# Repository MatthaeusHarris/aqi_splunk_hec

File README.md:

# Air Quality Data Logger for Splunk

This is the arduino-based firmware for an ESP8266-based device which will monitor air quality by means of a PMS7003 Air Quality Sensor and upload the resulting data to a Splunk HTTP Event Collector.  

## Configuration

On first flash, the device will create its own wifi access point "WifiManager" and wait to be configured.  Simply connect to the access point and open the [Configuration Page](http://192.168.4.1) to configure the device.  All fields are required.  These settings are stored in flash memory and will persist across power cycles.

Settings are as follows:
* Splunk Server: FQDN of the server on which Splunk is running
* Splunk Port:  TCP port on which the HEC is listening
* Token: HEC token
* Index: the Splunk index that will receive this data
* Sourcetype: the sourcetype that shall accompany this data

If a new configuration is required, reboot the device (either with the reboot button on the ESP8266 or via a power cycle), then hold the flash button down for three seconds.  Do not hold the flash button down while rebooting, as this puts the ESP8266 into another mode. 

## Debugging

The device will also log debug information to a serial port on the ESP8266's USB port at 115200,8,N,1.  Once the device is booted, this consists of a single line of data containing the current AQI, PM2.5, and PM10 readings once per second.

## Screen

The TFT_eSPI library is required to compile the firmware, but the device will work without one connected.  The code assumes a 128x128 screen, but should be easy enough to modify if desired.

## Dependencies

This firmware depends on the following libraries:
* TFT_eSPI
* ArduinoJson
* WifiManager

## Wiring

Power the PMSx003 with 5V.  Connect only the TX and RX pins to D3 and D4, respectively.

If you wish to connect an LCD screen, set up your User_Setup.h file according to the screen you are using.  This was tested with a ST7735 green tab 3 screen.

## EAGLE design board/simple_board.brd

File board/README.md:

# Board Files

Eagle 9.2.2, nothing fancy, just routing and layout for a NodeMCU and pin headers for a ST7735 screen and the PMSx003 air quality monitor.

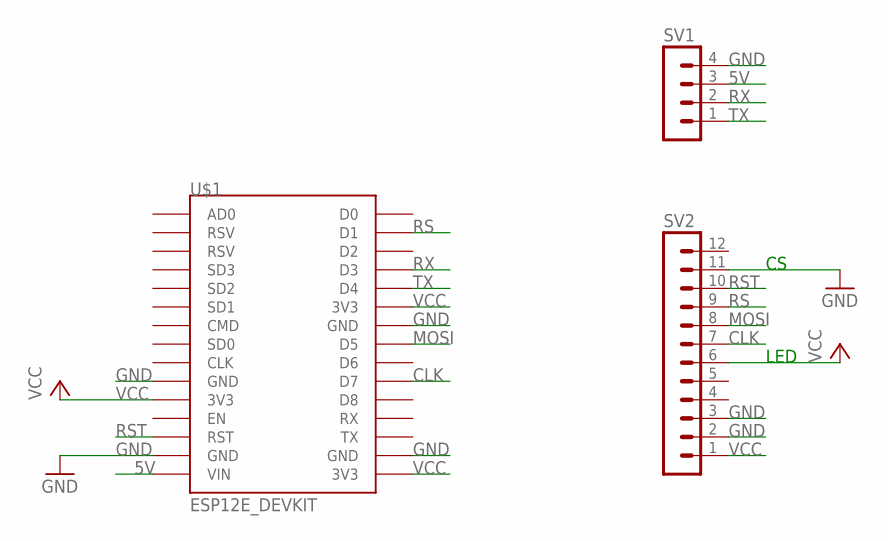
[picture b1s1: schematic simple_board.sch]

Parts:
SV1: MA04-1
SV2: MA12-1
U$1: ESP12E_DEVKIT

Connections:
5V: SV1.3, U$1.VIN
CLK: SV2.7, U$1.D7
GND: SV1.4, SV2.2, SV2.3, SV2.11, U$1.GND@0 (GND), U$1.GND@1 (GND), U$1.GND@2 (GND), U$1.GND@3 (GND)
MOSI: SV2.8, U$1.D5
RS: SV2.9, U$1.D1
RST: SV2.10, U$1.RST
RX: SV1.2, U$1.D3
TX: SV1.1, U$1.D4
VCC: SV2.1, SV2.6, U$1.3V3@0 (3V3), U$1.3V3@1 (3V3), U$1.3V3@2 (3V3)

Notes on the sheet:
LED

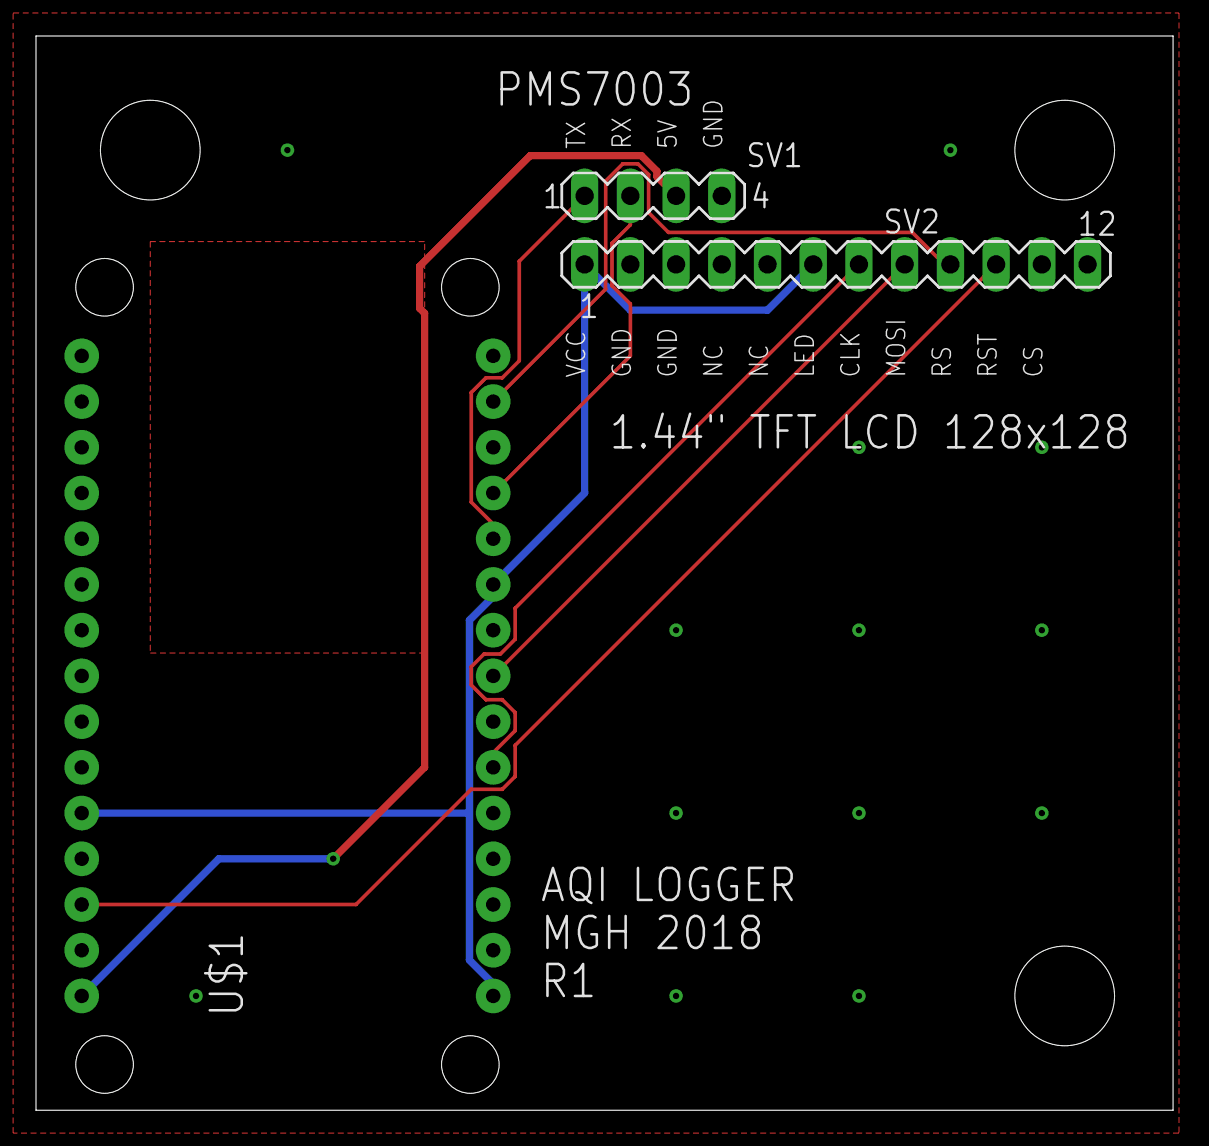
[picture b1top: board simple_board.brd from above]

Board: 2 copper layers, 63.2 x 59.7 mm, 3 parts (0 on the bottom side), 9 nets.

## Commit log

2018-12-04 Add license and readme
2018-12-04 Add eagle files
2019-11-03 Working with selectable WiFi config
2019-11-03 Smooth fonts, boyscoutting, blinker on TFT
2019-11-03 Boyscoutting, clean up UX a bit
2019-11-03 random password, chip-id ssid, qrcode wifi setup
2019-11-06 Fix a bug on wifi connect
2019-11-06 Increase limits for url and auth, fix broken splunk hec init
2019-11-07 Add default device_location
2019-11-07 ignore .vscode
